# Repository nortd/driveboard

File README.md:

# driveboard
Reference hardware for the DriveboardApp

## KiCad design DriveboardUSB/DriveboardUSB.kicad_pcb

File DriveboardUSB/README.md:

TODO
----

- metal box, change a few things so easier
  - box frame with two aluminum extrusions
  - change modular and DC jacks to vertical throughole 
- pcb changes
  - eliminate high/low feature, laser:pin5 wire to 5V, PD6 to aux jack
  - 5V from laser by default, 5V PSU optional
  - sense/control shield to case via laser wire
  - optionally different voltage for AIR/AUX

Logic Changes
-------------

- internally inverted sensors
  - x1,x2,y1,y2,z1,z2,door1,door2,chiller
- laser pwm inverted, connect to TL instead of TH
- PD5 is now laser PWM
- PD6 switches between full/half laser power mode
- 

Specs
-----
- board thickness: 0.062", 1.6mm
- hole > 15mil
- clearande > 7min
- copper: 1oz
- 1.4mm -> 3A
- 2.8 -> 5A
- 3.5mm -> 6A

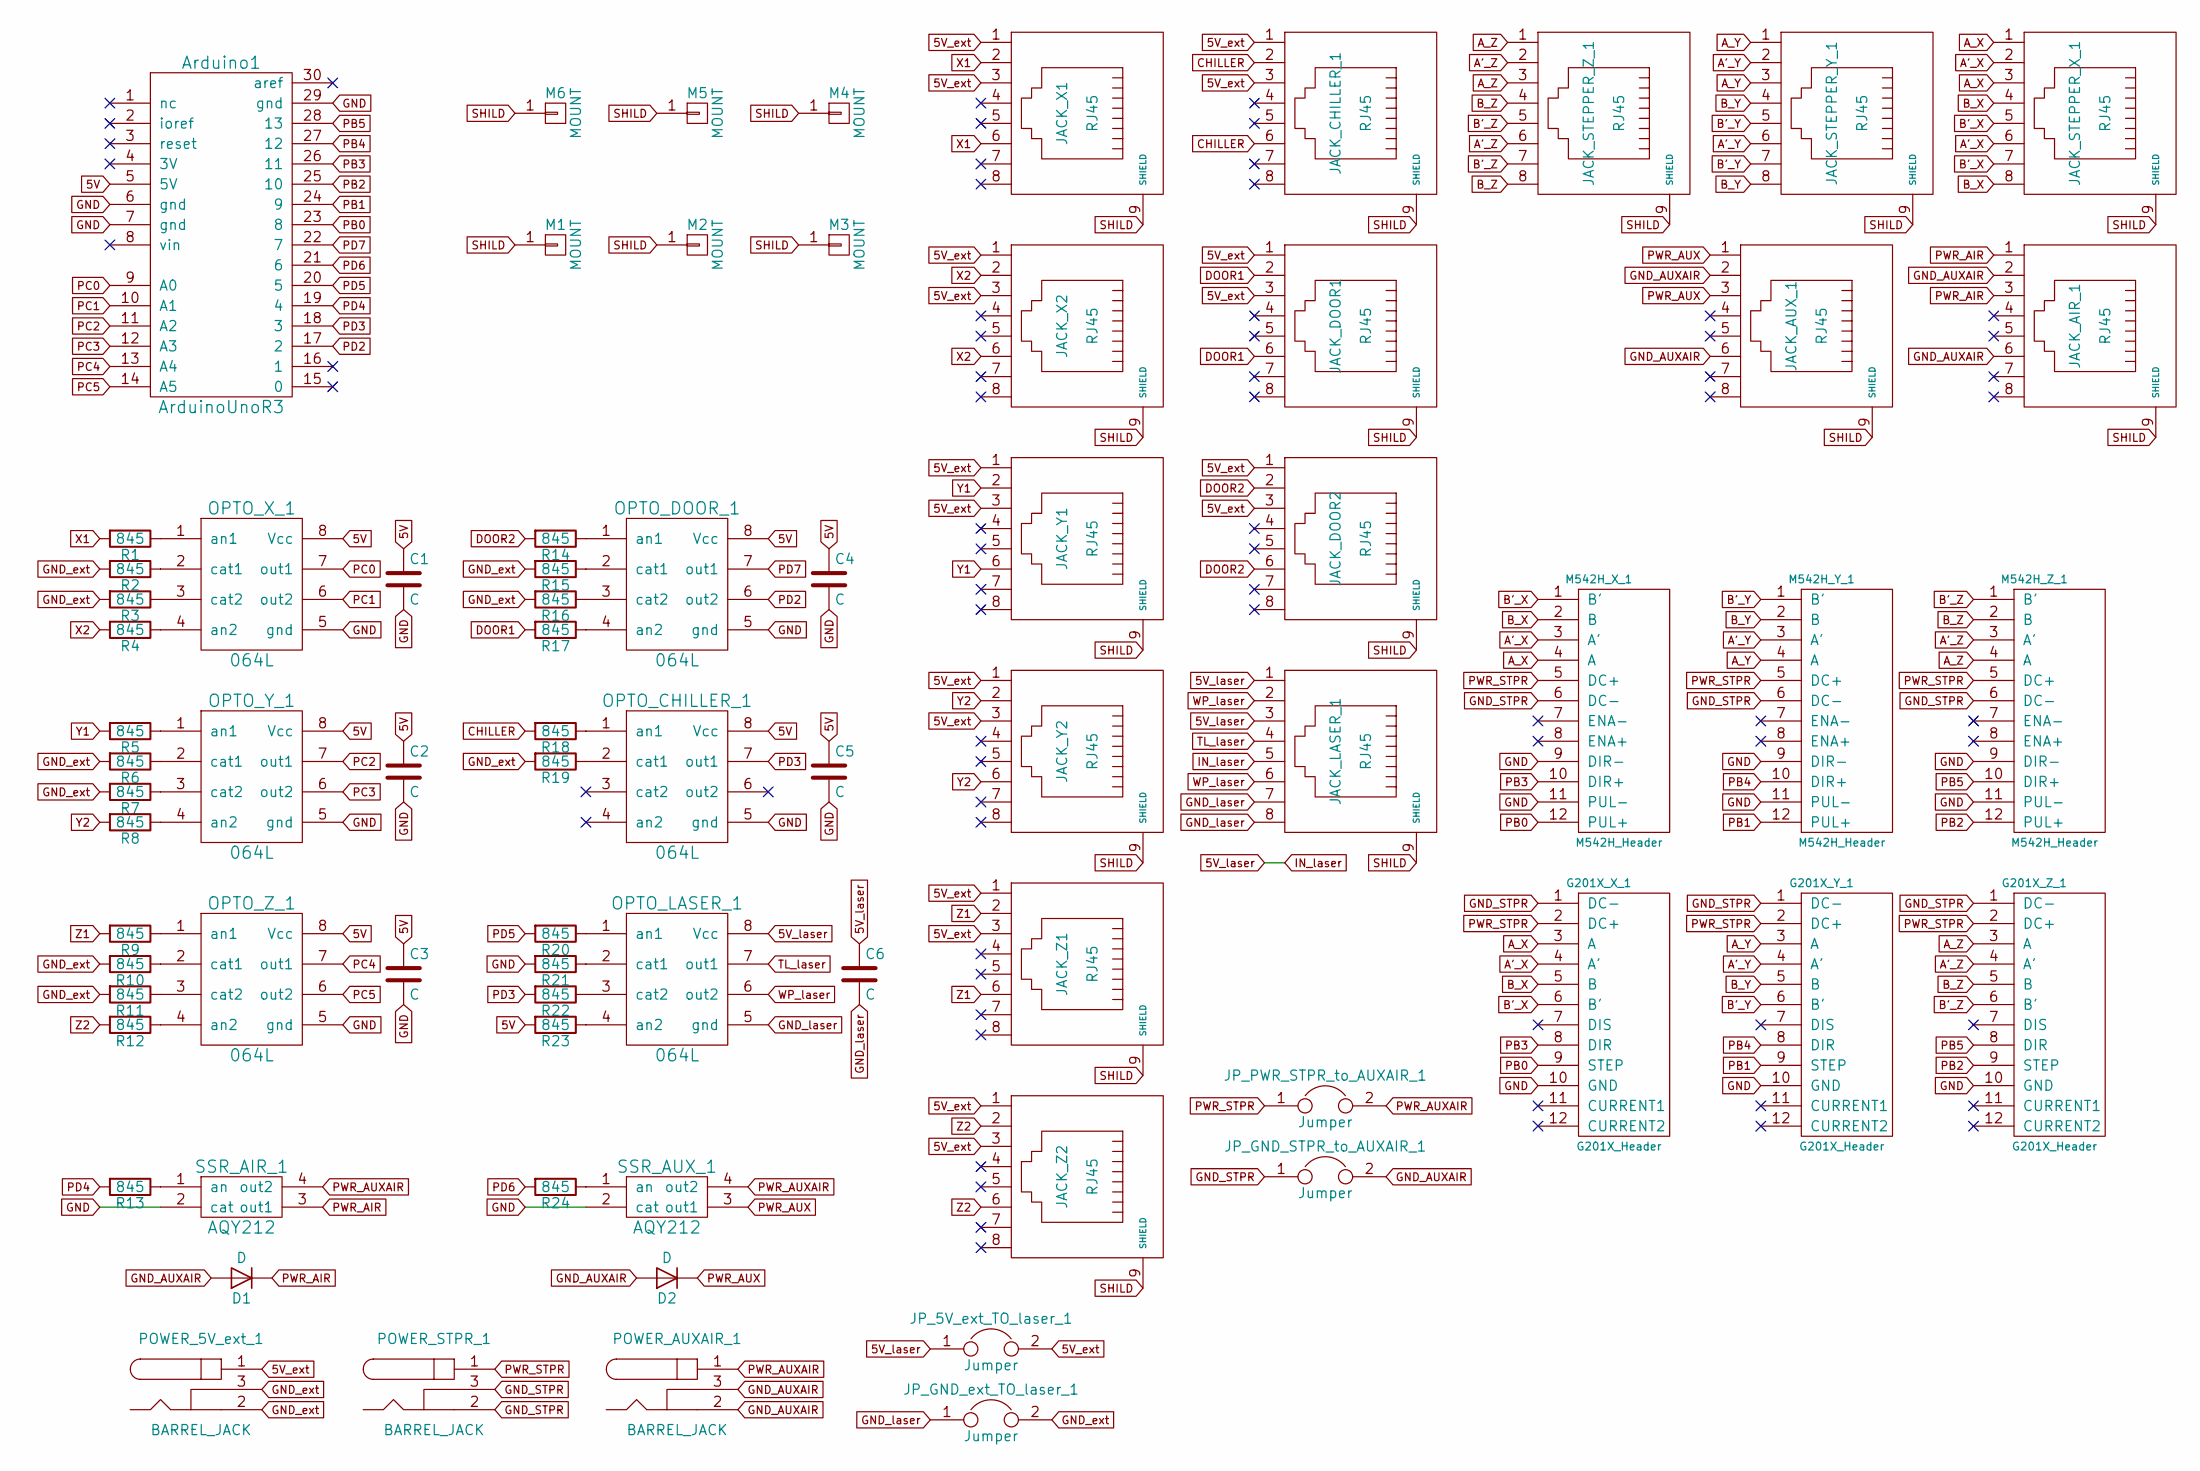
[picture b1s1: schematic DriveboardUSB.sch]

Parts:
Arduino1: ArduinoUnoR3
C1, C2, C3, C4, C5, C6: C; C_1206
D1, D2: D; SMD-1206_Pol; Part# CURN102-HF
G201X_X_1, G201X_Y_1, G201X_Z_1: G201X_Header; GeckoHeader
JACK_AIR_1: RJ45; RJHSE3380
JACK_AUX_1: RJ45; RJHSE3380
JACK_CHILLER_1: RJ45; RJHSE3380
JACK_DOOR1, JACK_DOOR2: RJ45; RJHSE3380
JACK_LASER_1: RJ45; RJHSE3380
JACK_STEPPER_X_1: RJ45; RJHSE3380
JACK_STEPPER_Y_1: RJ45; RJHSE3380
JACK_STEPPER_Z_1: RJ45; RJHSE3380
JACK_X1, JACK_X2: RJ45; RJHSE3380
JACK_Y1, JACK_Y2: RJ45; RJHSE3380
JACK_Z1, JACK_Z2: RJ45; RJHSE3380
JP_5V_ext_TO_laser_1: Jumper; Pin_Header_Straight_1x02_Pitch2.54mm
JP_GND_STPR_to_AUXAIR_1: Jumper; Pin_Header_Straight_1x02_Pitch2.54mm
JP_GND_ext_TO_laser_1: Jumper; Pin_Header_Straight_1x02_Pitch2.54mm
JP_PWR_STPR_to_AUXAIR_1: Jumper; Pin_Header_Straight_1x02_Pitch2.54mm
M1, M2, M3, M4, M5, M6: MOUNT; 1pin
M542H_X_1, M542H_Y_1, M542H_Z_1: M542H_Header
OPTO_CHILLER_1: 064L; SO-8
OPTO_DOOR_1: 064L; SO-8
OPTO_LASER_1: 064L; SO-8
OPTO_X_1: 064L; SO-8
OPTO_Y_1: 064L; SO-8
OPTO_Z_1: 064L; SO-8
POWER_5V_ext_1: BARREL_JACK; BARREL_JACK_VERT; Part# PJ-002AH-SMT-TR
POWER_AUXAIR_1: BARREL_JACK; BARREL_JACK_VERT; Part# PJ-002AH-SMT-TR
POWER_STPR_1: BARREL_JACK; BARREL_JACK_VERT; Part# PJ-002AH-SMT-TR
R1, R2, R3, R4, R5, R6, R7, R8, R9, R10, R11, R12, R13, R14, R15, R16, R17, R18, R19, R20, R21, R22, R23, R24: 845; R_1206
SSR_AIR_1: AQY212; DIP-4_SMD
SSR_AUX_1: AQY212; DIP-4_SMD

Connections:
5V: Arduino1.5 (5V), C1.1, C2.1, C3.1, C4.1, C5.1, OPTO_CHILLER_1.8 (Vcc), OPTO_DOOR_1.8 (Vcc), OPTO_X_1.8 (Vcc), OPTO_Y_1.8 (Vcc), OPTO_Z_1.8 (Vcc), R23.2
5V_ext: JACK_CHILLER_1.1, JACK_CHILLER_1.3, JACK_DOOR1.1, JACK_DOOR1.3, JACK_DOOR2.1, JACK_DOOR2.3, JACK_X1.1, JACK_X1.3, JACK_X2.1, JACK_X2.3, JACK_Y1.1, JACK_Y1.3, JACK_Y2.1, JACK_Y2.3, JACK_Z1.1, JACK_Z1.3, JACK_Z2.1, JACK_Z2.3, JP_5V_ext_TO_laser_1.2, POWER_5V_ext_1.1
5V_laser: C6.1, JACK_LASER_1.1, JACK_LASER_1.3, JACK_LASER_1.5, JP_5V_ext_TO_laser_1.1, OPTO_LASER_1.8 (Vcc)
A'_X: G201X_X_1.4 (A'), JACK_STEPPER_X_1.2, JACK_STEPPER_X_1.6, M542H_X_1.3 (A')
A'_Y: G201X_Y_1.4 (A'), JACK_STEPPER_Y_1.2, JACK_STEPPER_Y_1.6, M542H_Y_1.3 (A')
A'_Z: G201X_Z_1.4 (A'), JACK_STEPPER_Z_1.2, JACK_STEPPER_Z_1.6, M542H_Z_1.3 (A')
A_X: G201X_X_1.3 (A), JACK_STEPPER_X_1.1, JACK_STEPPER_X_1.3, M542H_X_1.4 (A)
A_Y: G201X_Y_1.3 (A), JACK_STEPPER_Y_1.1, JACK_STEPPER_Y_1.3, M542H_Y_1.4 (A)
A_Z: G201X_Z_1.3 (A), JACK_STEPPER_Z_1.1, JACK_STEPPER_Z_1.3, M542H_Z_1.4 (A)
B'_X: G201X_X_1.6 (B'), JACK_STEPPER_X_1.5, JACK_STEPPER_X_1.7, M542H_X_1.1 (B')
B'_Y: G201X_Y_1.6 (B'), JACK_STEPPER_Y_1.5, JACK_STEPPER_Y_1.7, M542H_Y_1.1 (B')
B'_Z: G201X_Z_1.6 (B'), JACK_STEPPER_Z_1.5, JACK_STEPPER_Z_1.7, M542H_Z_1.1 (B')
B_X: G201X_X_1.5 (B), JACK_STEPPER_X_1.4, JACK_STEPPER_X_1.8, M542H_X_1.2 (B)
B_Y: G201X_Y_1.5 (B), JACK_STEPPER_Y_1.4, JACK_STEPPER_Y_1.8, M542H_Y_1.2 (B)
B_Z: G201X_Z_1.5 (B), JACK_STEPPER_Z_1.4, JACK_STEPPER_Z_1.8, M542H_Z_1.2 (B)
CHILLER: JACK_CHILLER_1.2, JACK_CHILLER_1.6, R18.2
DOOR1: JACK_DOOR1.2, JACK_DOOR1.6, R17.2
DOOR2: JACK_DOOR2.2, JACK_DOOR2.6, R14.2
GND: Arduino1.6 (gnd), Arduino1.7 (gnd), Arduino1.29 (gnd), C1.2, C2.2, C3.2, C4.2, C5.2, G201X_X_1.10 (GND), G201X_Y_1.10 (GND), G201X_Z_1.10 (GND), M542H_X_1.9 (DIR-), M542H_X_1.11 (PUL-), M542H_Y_1.9 (DIR-), M542H_Y_1.11 (PUL-), M542H_Z_1.9 (DIR-), M542H_Z_1.11 (PUL-), OPTO_CHILLER_1.5 (gnd), OPTO_DOOR_1.5 (gnd), OPTO_X_1.5 (gnd), OPTO_Y_1.5 (gnd), OPTO_Z_1.5 (gnd), R21.2, SSR_AIR_1.2 (cat), SSR_AUX_1.2 (cat)
GND_AUXAIR: D1.2 (A), D2.2 (A), JACK_AIR_1.2, JACK_AIR_1.6, JACK_AUX_1.2, JACK_AUX_1.6, JP_GND_STPR_to_AUXAIR_1.2, POWER_AUXAIR_1.2, POWER_AUXAIR_1.3
GND_STPR: G201X_X_1.1 (DC-), G201X_Y_1.1 (DC-), G201X_Z_1.1 (DC-), JP_GND_STPR_to_AUXAIR_1.1, M542H_X_1.6 (DC-), M542H_Y_1.6 (DC-), M542H_Z_1.6 (DC-), POWER_STPR_1.2, POWER_STPR_1.3
GND_ext: JP_GND_ext_TO_laser_1.2, POWER_5V_ext_1.2, POWER_5V_ext_1.3, R2.2, R3.2, R6.2, R7.2, R10.2, R11.2, R15.2, R16.2, R19.2
GND_laser: C6.2, JACK_LASER_1.7, JACK_LASER_1.8, JP_GND_ext_TO_laser_1.1, OPTO_LASER_1.5 (gnd)
unnamed: OPTO_CHILLER_1.1 (an1), R18.1
unnamed: OPTO_CHILLER_1.2 (cat1), R19.1
unnamed: OPTO_DOOR_1.1 (an1), R14.1
unnamed: OPTO_DOOR_1.2 (cat1), R15.1
unnamed: OPTO_DOOR_1.3 (cat2), R16.1
unnamed: OPTO_DOOR_1.4 (an2), R17.1
unnamed: OPTO_LASER_1.1 (an1), R20.1
unnamed: OPTO_LASER_1.2 (cat1), R21.1
unnamed: OPTO_LASER_1.3 (cat2), R22.1
unnamed: OPTO_LASER_1.4 (an2), R23.1
unnamed: OPTO_X_1.1 (an1), R1.1
unnamed: OPTO_X_1.2 (cat1), R2.1
unnamed: OPTO_X_1.3 (cat2), R3.1
unnamed: OPTO_X_1.4 (an2), R4.1
unnamed: OPTO_Y_1.1 (an1), R5.1
unnamed: OPTO_Y_1.2 (cat1), R6.1
unnamed: OPTO_Y_1.3 (cat2), R7.1
unnamed: OPTO_Y_1.4 (an2), R8.1
unnamed: OPTO_Z_1.1 (an1), R9.1
unnamed: OPTO_Z_1.2 (cat1), R10.1
unnamed: OPTO_Z_1.3 (cat2), R11.1
unnamed: OPTO_Z_1.4 (an2), R12.1
unnamed: R13.1, SSR_AIR_1.1 (an)
unnamed: R24.1, SSR_AUX_1.1 (an)
PB0: Arduino1.23 (8), G201X_X_1.9 (STEP), M542H_X_1.12 (PUL+)
PB1: Arduino1.24 (9), G201X_Y_1.9 (STEP), M542H_Y_1.12 (PUL+)
PB2: Arduino1.25 (10), G201X_Z_1.9 (STEP), M542H_Z_1.12 (PUL+)
PB3: Arduino1.26 (11), G201X_X_1.8 (DIR), M542H_X_1.10 (DIR+)
PB4: Arduino1.27 (12), G201X_Y_1.8 (DIR), M542H_Y_1.10 (DIR+)
PB5: Arduino1.28 (13), G201X_Z_1.8 (DIR), M542H_Z_1.10 (DIR+)
PC0: Arduino1.9 (A0), OPTO_X_1.7 (out1)
PC1: Arduino1.10 (A1), OPTO_X_1.6 (out2)
PC2: Arduino1.11 (A2), OPTO_Y_1.7 (out1)
PC3: Arduino1.12 (A3), OPTO_Y_1.6 (out2)
PC4: Arduino1.13 (A4), OPTO_Z_1.7 (out1)
PC5: Arduino1.14 (A5), OPTO_Z_1.6 (out2)
PD2: Arduino1.17 (2), OPTO_DOOR_1.6 (out2)
PD3: Arduino1.18 (3), OPTO_CHILLER_1.7 (out1), R22.2
PD4: Arduino1.19 (4), R13.2
PD5: Arduino1.20 (5), R20.2
PD6: Arduino1.21 (6), R24.2
PD7: Arduino1.22 (7), OPTO_DOOR_1.7 (out1)
PWR_AIR: D1.1 (K), JACK_AIR_1.1, JACK_AIR_1.3, SSR_AIR_1.3 (out1)
PWR_AUX: D2.1 (K), JACK_AUX_1.1, JACK_AUX_1.3, SSR_AUX_1.3 (out1)
PWR_AUXAIR: JP_PWR_STPR_to_AUXAIR_1.2, POWER_AUXAIR_1.1, SSR_AIR_1.4 (out2), SSR_AUX_1.4 (out2)
PWR_STPR: G201X_X_1.2 (DC+), G201X_Y_1.2 (DC+), G201X_Z_1.2 (DC+), JP_PWR_STPR_to_AUXAIR_1.1, M542H_X_1.5 (DC+), M542H_Y_1.5 (DC+), M542H_Z_1.5 (DC+), POWER_STPR_1.1
SHILD: JACK_AIR_1.9 (SHIELD), JACK_AUX_1.9 (SHIELD), JACK_CHILLER_1.9 (SHIELD), JACK_DOOR1.9 (SHIELD), JACK_DOOR2.9 (SHIELD), JACK_LASER_1.9 (SHIELD), JACK_STEPPER_X_1.9 (SHIELD), JACK_STEPPER_Y_1.9 (SHIELD), JACK_STEPPER_Z_1.9 (SHIELD), JACK_X1.9 (SHIELD), JACK_X2.9 (SHIELD), JACK_Y1.9 (SHIELD), JACK_Y2.9 (SHIELD), JACK_Z1.9 (SHIELD), JACK_Z2.9 (SHIELD), M1.1, M2.1, M3.1, M4.1, M5.1, M6.1
TL_laser: JACK_LASER_1.4, OPTO_LASER_1.7 (out1)
WP_laser: JACK_LASER_1.2, JACK_LASER_1.6, OPTO_LASER_1.6 (out2)
X1: JACK_X1.2, JACK_X1.6, R1.2
X2: JACK_X2.2, JACK_X2.6, R4.2
Y1: JACK_Y1.2, JACK_Y1.6, R5.2
Y2: JACK_Y2.2, JACK_Y2.6, R8.2
Z1: JACK_Z1.2, JACK_Z1.6, R9.2
Z2: JACK_Z2.2, JACK_Z2.6, R12.2

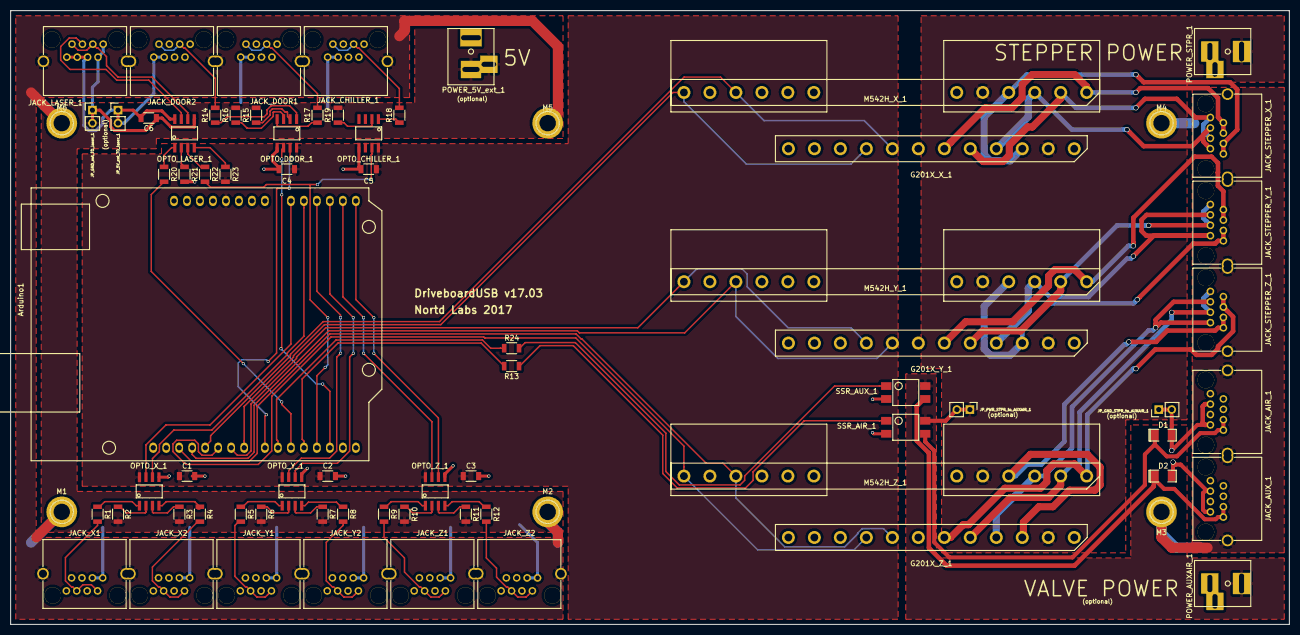
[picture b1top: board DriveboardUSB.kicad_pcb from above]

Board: 2 copper layers, 250.0 x 120.0 mm, 75 parts (0 on the bottom side), 78 nets.

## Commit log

2017-02-11 board with top jacks, started working
2017-02-14 running traces
2017-02-14 all traces, beautifying
2017-02-15 DRC'd
2017-02-15 generated gerber for v17.02
2017-02-15 generated gerber for v17.02 - with mount holes
2017-02-15 as RFQ'd
2017-02-19 RFQ, take 2
2017-02-27 docs
2017-04-11 bom added
2017-10-19 using template from WaveGlide project
2017-10-19 Create CNAME
2017-10-19 optimill
2019-02-24 more design/order files
2019-02-24 images
